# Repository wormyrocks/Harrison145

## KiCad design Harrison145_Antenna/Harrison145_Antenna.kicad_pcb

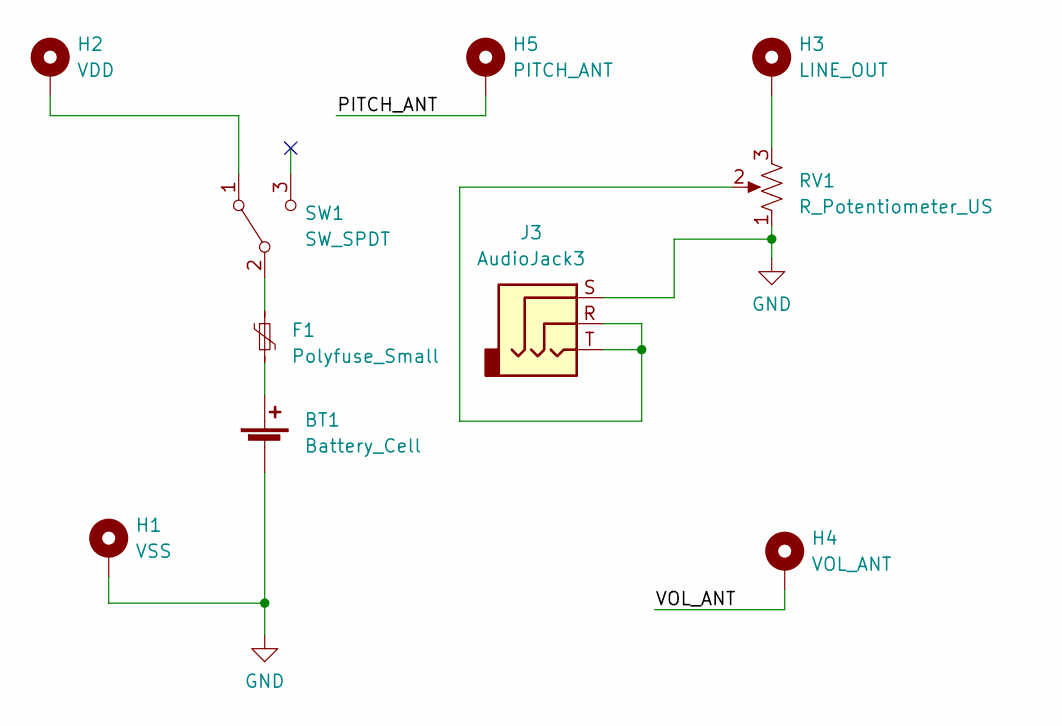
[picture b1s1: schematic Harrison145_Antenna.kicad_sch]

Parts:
BT1: Battery_Cell; 9V_Bat
F1: Polyfuse_Small; Fuse_1812_4532Metric_Pad1.30x3.40mm_HandSolder
H1: VSS; SMTSO-M4
H2: VDD; SMTSO-M4
H3: LINE_OUT; SMTSO-M4
H4: VOL_ANT; SMTSO-M4
H5: PITCH_ANT; SMTSO-M4
J3: AudioJack3; Jack_3.5mm_CUI_SJ-3523-SMT_Horizontal
RV1: R_Potentiometer_US; PTV09A3015FB103
SW1: SW_SPDT; CSS1210TB

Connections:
/PITCH_ANT: H5.1
/VOL_ANT: H4.1
GND: BT1.2 (-), H1.1, J3.S, RV1.1
unnamed: BT1.1 (+), F1.2
unnamed: H3.1, RV1.3
unnamed: J3.R, J3.T, RV1.2
unnamed: H2.1, SW1.1 (A)
unnamed: F1.1, SW1.2 (B)

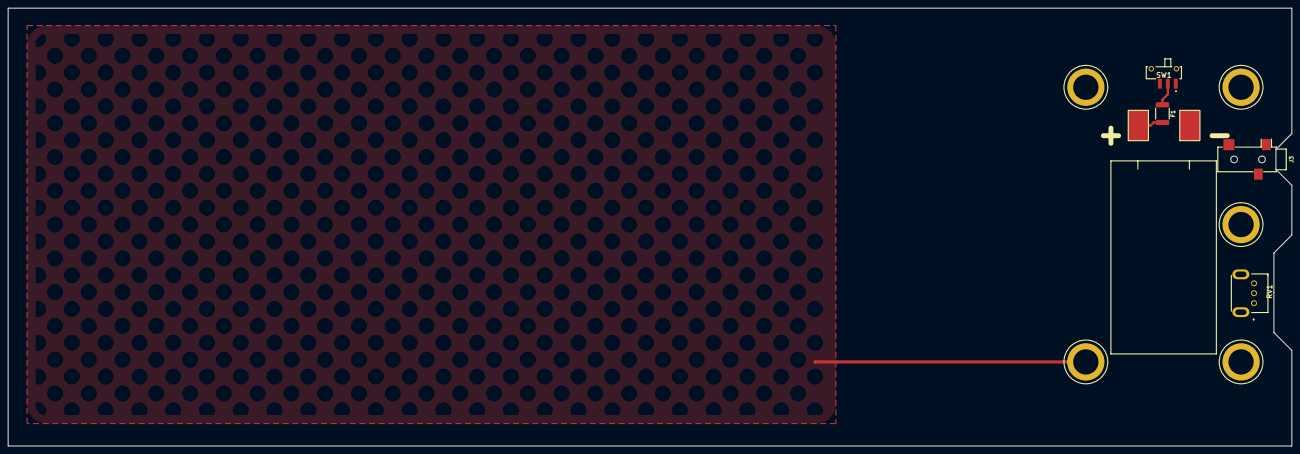
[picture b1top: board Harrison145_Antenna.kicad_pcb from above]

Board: 2 copper layers, 322.5 x 110.0 mm, 10 parts (0 on the bottom side), 6 nets.

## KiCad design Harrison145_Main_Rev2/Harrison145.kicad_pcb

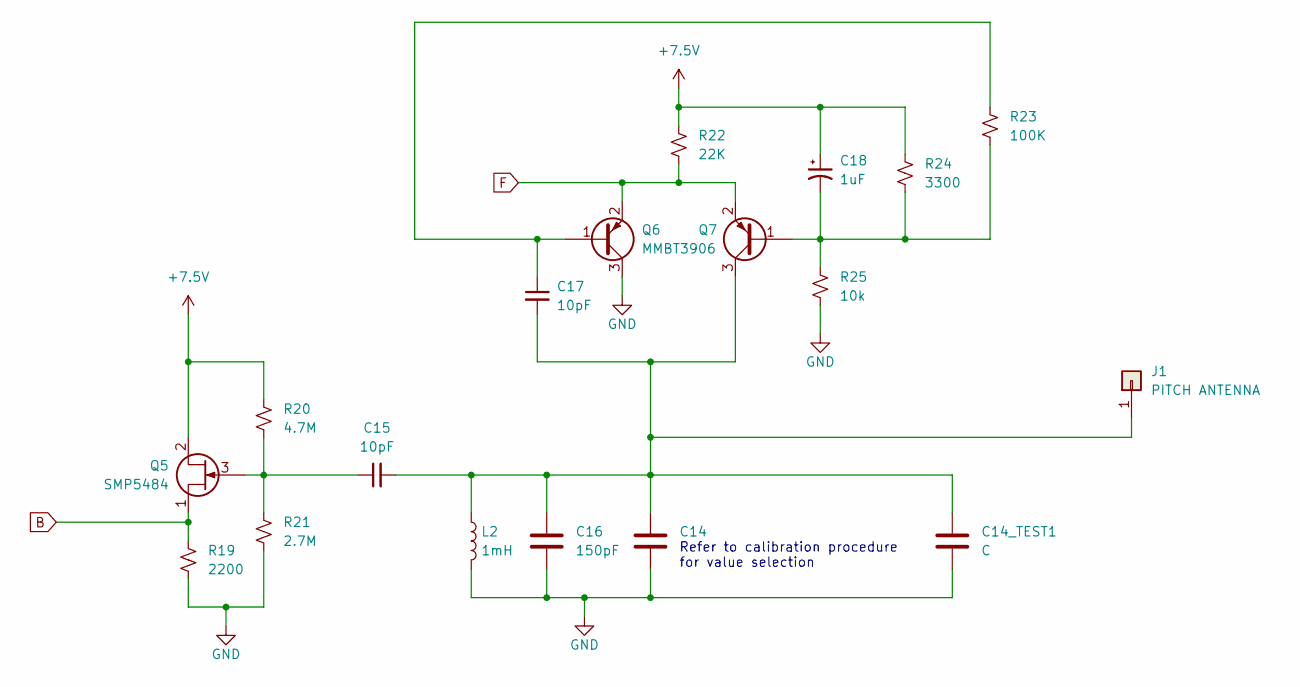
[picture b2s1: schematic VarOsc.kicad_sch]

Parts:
C14: C_Mica; C_0805_2012Metric_Pad1.18x1.45mm_HandSolder
C14_TEST1: C; C_Disc_D3.0mm_W1.6mm_P2.50mm
C15, C17: 10pF; C_0603_1608Metric
C16: 150pF; C_1210_3225Metric_Pad1.33x2.70mm_HandSolder
C18: 1uF; CP_EIA-2012-12_Kemet-R_Pad1.30x1.05mm_HandSolder
J1: PITCH ANTENNA; MountingHole_4.3mm_M4_Pad_Via
L2: 1mH; L_1812_4532Metric
Q5: SMP5484; SOT-23
Q6, Q7: MMBT3906; SOT-23
R19: 2200; R_0603_1608Metric
R20: 4.7M; R_0603_1608Metric
R21: 2.7M; R_0603_1608Metric
R22: 22K; R_0603_1608Metric
R23: 100K; R_0603_1608Metric
R24: 3300; R_0603_1608Metric
R25: 10k; R_0603_1608Metric

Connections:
+7.5V: C18.1, Q5.2 (D), R20.1, R22.1, R24.1; also elsewhere on the board
B: Q5.1 (S), R19.1; also elsewhere on the board
F: Q6.2 (E), Q7.2 (E), R22.2; also elsewhere on the board
GND: C14.2, C14_TEST1.2, C16.2, L2.2, Q6.3 (C), R19.2, R21.2, R25.2; also elsewhere on the board
unnamed: C14.1, C14_TEST1.1, C15.2, C16.1, C17.2, J1.1, L2.1, Q7.3 (C)
unnamed: C15.1, Q5.3 (G), R20.2, R21.1
unnamed: C17.1, Q6.1 (B), R23.1
unnamed: C18.2, Q7.1 (B), R23.2, R24.2, R25.1

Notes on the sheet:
Refer to calibration procedure for value selection

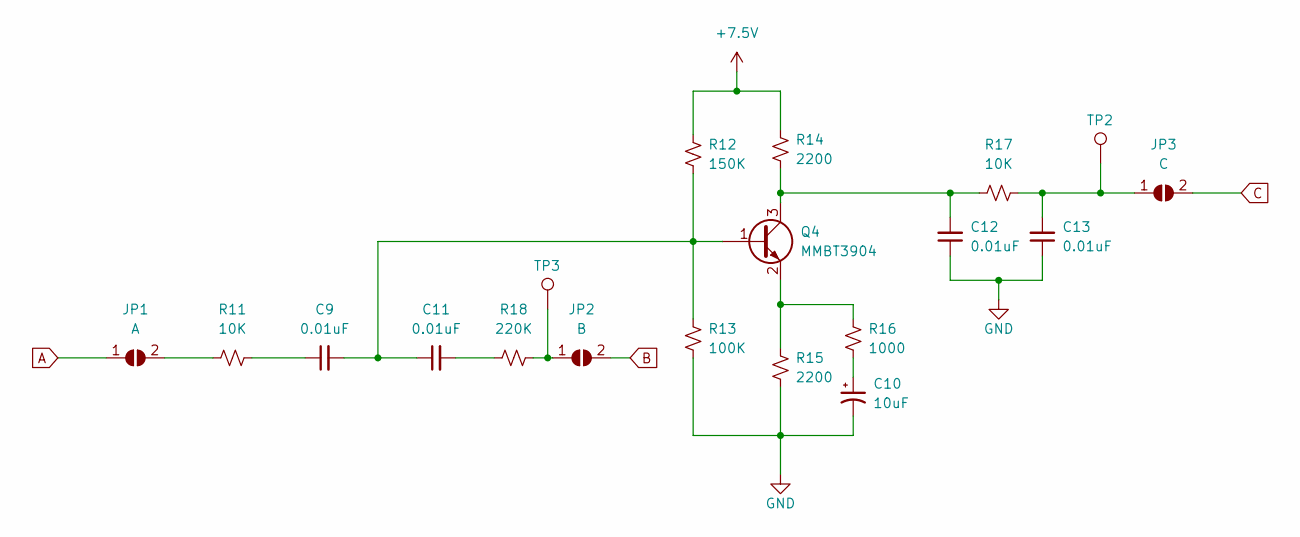
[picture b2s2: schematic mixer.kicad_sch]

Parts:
C9, C11, C12, C13: 0.01uF; C_0603_1608Metric
C10: 10uF; CP_EIA-3216-18_Kemet-A
JP1: A; SolderJumper-2_P1.3mm_Open_RoundedPad1.0x1.5mm
JP2: B; SolderJumper-2_P1.3mm_Open_RoundedPad1.0x1.5mm
JP3: C; SolderJumper-2_P1.3mm_Open_RoundedPad1.0x1.5mm
Q4: MMBT3904; SOT-23
R11, R17: 10K; R_0603_1608Metric
R12: 150K; R_0603_1608Metric
R13: 100K; R_0603_1608Metric
R14, R15: 2200; R_0603_1608Metric
R16: 1000; R_0603_1608Metric
R18: 220K; R_0603_1608Metric
TP2, TP3: TestPoint; TestPoint_Loop_D1.80mm_Drill1.0mm_Beaded

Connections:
+7.5V: R12.2, R14.2; also elsewhere on the board
A: JP1.1 (A); also elsewhere on the board
B: JP2.2 (B); also elsewhere on the board
C: JP3.2 (B); also elsewhere on the board
GND: C10.2, C12.1, C13.1, R13.1, R15.1; also elsewhere on the board
unnamed: C9.1, R11.2
unnamed: C10.1, R16.1
unnamed: C11.2, R18.1
unnamed: JP1.2 (B), R11.1
unnamed: JP2.1 (A), R18.2, TP3.1
unnamed: C13.2, JP3.1 (A), R17.2, TP2.1
unnamed: C9.2, C11.1, Q4.1 (B), R12.1, R13.2
unnamed: C12.2, Q4.3 (C), R14.1, R17.1
unnamed: Q4.2 (E), R15.2, R16.2

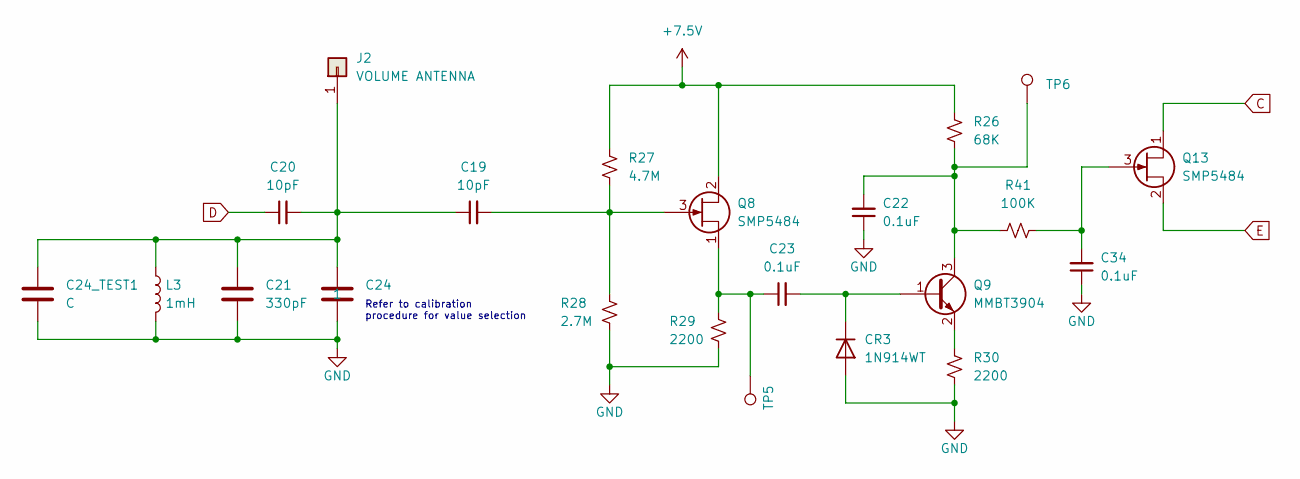
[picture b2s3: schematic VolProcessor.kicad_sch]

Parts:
C19, C20: 10pF; C_0603_1608Metric
C21: 330pF; C_1812_4532Metric_Pad1.57x3.40mm_HandSolder
C22, C23, C34: 0.1uF; C_0603_1608Metric
C24: C_Mica; C_0805_2012Metric_Pad1.18x1.45mm_HandSolder
C24_TEST1: C; C_Disc_D3.0mm_W1.6mm_P2.50mm
CR3: 1N914WT; D_SOD-523
J2: VOLUME ANTENNA; MountingHole_4.3mm_M4_Pad_Via
L3: 1mH; L_1812_4532Metric
Q8, Q13: SMP5484; SOT-23
Q9: MMBT3904; SOT-23
R26: 68K; R_0603_1608Metric
R27: 4.7M; R_0603_1608Metric
R28: 2.7M; R_0603_1608Metric
R29, R30: 2200; R_0603_1608Metric
R41: 100K; R_0603_1608Metric
TP5, TP6: TestPoint; TestPoint_Loop_D1.80mm_Drill1.0mm_Beaded

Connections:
+7.5V: Q8.2 (D), R26.1, R27.1; also elsewhere on the board
C: Q13.1 (S); also elsewhere on the board
D: C20.1; also elsewhere on the board
E: Q13.2 (D); also elsewhere on the board
GND: C21.2, C22.1, C24.2, C24_TEST1.2, C34.1, CR3.2 (A), L3.2, R28.2, R29.2, R30.2; also elsewhere on the board
unnamed: C23.2, CR3.1 (K), Q9.1 (B)
unnamed: C19.1, C20.2, C21.1, C24.1, C24_TEST1.1, J2.1, L3.1
unnamed: C19.2, Q8.3 (G), R27.2, R28.1
unnamed: C23.1, Q8.1 (S), R29.1, TP5.1
unnamed: C22.2, Q9.3 (C), R26.2, R41.1, TP6.1
unnamed: Q9.2 (E), R30.1
unnamed: C34.2, Q13.3 (G), R41.2

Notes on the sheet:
Refer to calibration procedure for value selection

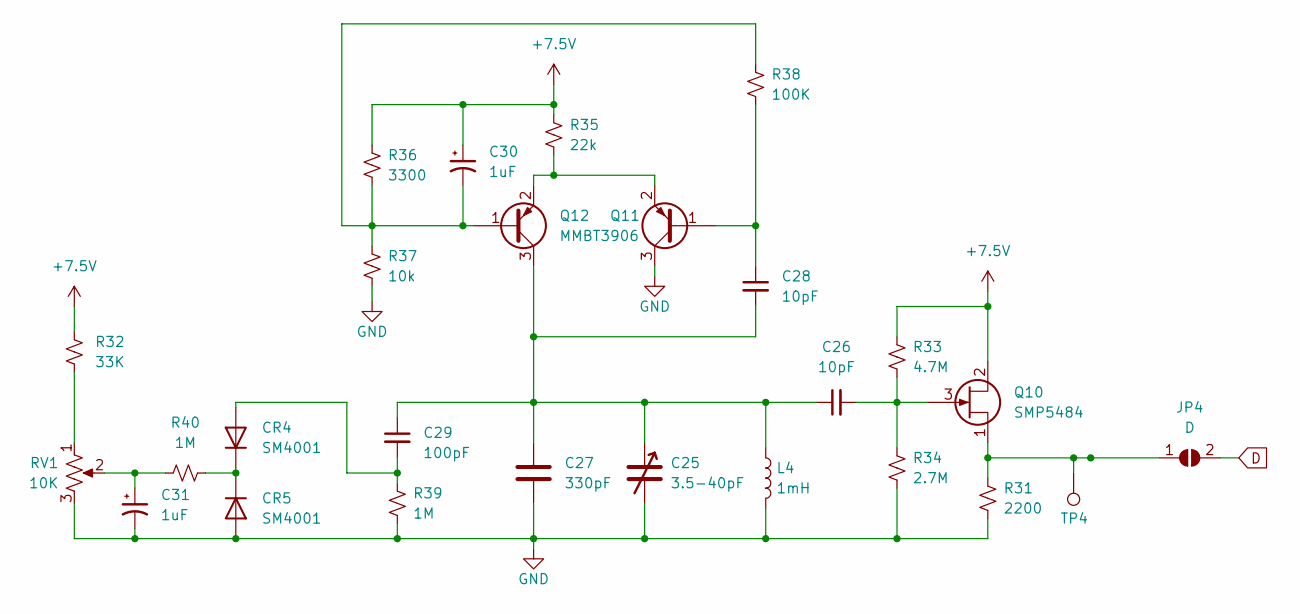
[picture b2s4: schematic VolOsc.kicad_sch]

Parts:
C25: 3.5-40pF; CAPV_JZ400
C26, C28: 10pF; C_0603_1608Metric
C27: 330pF; C_1812_4532Metric_Pad1.57x3.40mm_HandSolder
C29: 100pF; C_0603_1608Metric
C30, C31: 1uF; CP_EIA-2012-12_Kemet-R_Pad1.30x1.05mm_HandSolder
CR4, CR5: SM4001; D_MELF
JP4: D; SolderJumper-2_P1.3mm_Open_RoundedPad1.0x1.5mm
L4: 1mH; L_1812_4532Metric
Q10: SMP5484; SOT-23
Q11, Q12: MMBT3906; SOT-23
R31: 2200; R_0603_1608Metric
R32: 33K; R_0603_1608Metric
R33: 4.7M; R_0603_1608Metric
R34: 2.7M; R_0603_1608Metric
R35: 22k; R_0603_1608Metric
R36: 3300; R_0603_1608Metric
R37: 10k; R_0603_1608Metric
R38: 100K; R_0603_1608Metric
R39, R40: 1M; R_0603_1608Metric
RV1: 10K; PTV09A3015FB103
TP4: TestPoint; TestPoint_Loop_D1.80mm_Drill1.0mm_Beaded

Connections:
+7.5V: C30.1, Q10.2 (D), R32.1, R33.1, R35.2, R36.1; also elsewhere on the board
D: JP4.2 (B); also elsewhere on the board
GND: C25.2, C27.2, C31.2, CR5.2 (A), L4.2, Q11.3 (C), R31.2, R34.2, R37.2, R39.2, RV1.3; also elsewhere on the board
unnamed: C31.1, R40.1, RV1.2
unnamed: C29.2, CR4.2 (A), R39.1
unnamed: CR4.1 (K), CR5.1 (K), R40.2
unnamed: JP4.1 (A), Q10.1 (S), R31.1, TP4.1
unnamed: C26.2, Q10.3 (G), R33.2, R34.1
unnamed: C28.1, Q11.1 (B), R38.2
unnamed: Q11.2 (E), Q12.2 (E), R35.1
unnamed: C30.2, Q12.1 (B), R36.2, R37.1, R38.1
unnamed: C25.1, C26.1, C27.1, C28.2, C29.1, L4.1, Q12.3 (C)
unnamed: R32.2, RV1.1

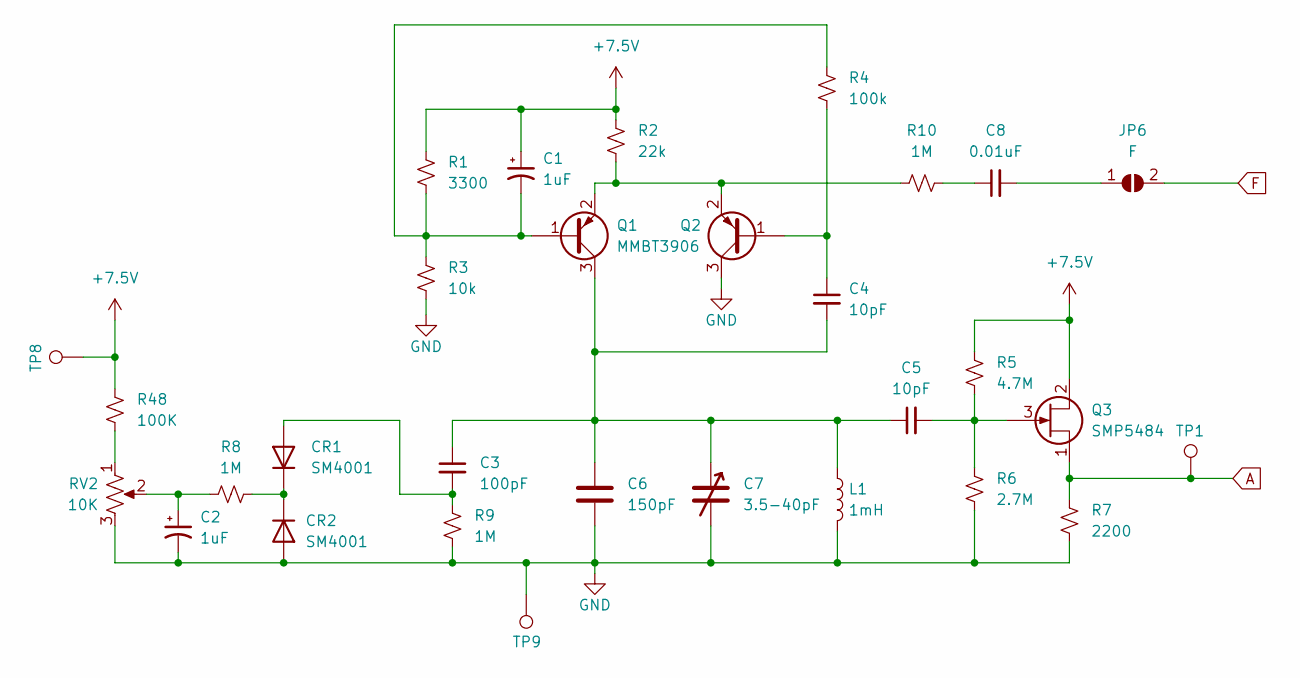
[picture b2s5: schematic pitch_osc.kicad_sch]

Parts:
C1, C2: 1uF; CP_EIA-2012-12_Kemet-R_Pad1.30x1.05mm_HandSolder
C3: 100pF; C_0603_1608Metric
C4, C5: 10pF; C_0603_1608Metric
C6: 150pF; C_1210_3225Metric_Pad1.33x2.70mm_HandSolder
C7: 3.5-40pF; CAPV_JZ400
C8: 0.01uF; C_0603_1608Metric
CR1, CR2: SM4001; D_MELF
JP6: F; SolderJumper-2_P1.3mm_Open_RoundedPad1.0x1.5mm
L1: 1mH; L_1812_4532Metric
Q1, Q2: MMBT3906; SOT-23
Q3: SMP5484; SOT-23
R1: 3300; R_0603_1608Metric
R2: 22k; R_0603_1608Metric
R3: 10k; R_0603_1608Metric
R4: 100k; R_0603_1608Metric
R5: 4.7M; R_0603_1608Metric
R6: 2.7M; R_0603_1608Metric
R7: 2200; R_0603_1608Metric
R8, R9, R10: 1M; R_0603_1608Metric
R48: 100K; R_0603_1608Metric
RV2: 10K; PTV09A3015FB103
TP1, TP8, TP9: TestPoint; TestPoint_Loop_D1.80mm_Drill1.0mm_Beaded

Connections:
+7.5V: C1.1, Q3.2 (D), R1.1, R2.2, R5.1, R48.1, TP8.1; also elsewhere on the board
A: Q3.1 (S), R7.1, TP1.1; also elsewhere on the board
F: JP6.2 (B); also elsewhere on the board
GND: C2.2, C6.2, C7.2, CR2.2 (A), L1.2, Q2.3 (C), R3.2, R6.2, R7.2, R9.2, RV2.3, TP9.1; also elsewhere on the board
unnamed: C2.1, R8.1, RV2.2
unnamed: C8.1, R10.2
unnamed: C3.2, CR1.2 (A), R9.1
unnamed: CR1.1 (K), CR2.1 (K), R8.2
unnamed: C8.2, JP6.1 (A)
unnamed: C1.2, Q1.1 (B), R1.2, R3.1, R4.1
unnamed: C3.1, C4.2, C5.1, C6.1, C7.1, L1.1, Q1.3 (C)
unnamed: Q1.2 (E), Q2.2 (E), R2.1, R10.1
unnamed: C4.1, Q2.1 (B), R4.2
unnamed: C5.2, Q3.3 (G), R5.2, R6.1
unnamed: R48.2, RV2.1

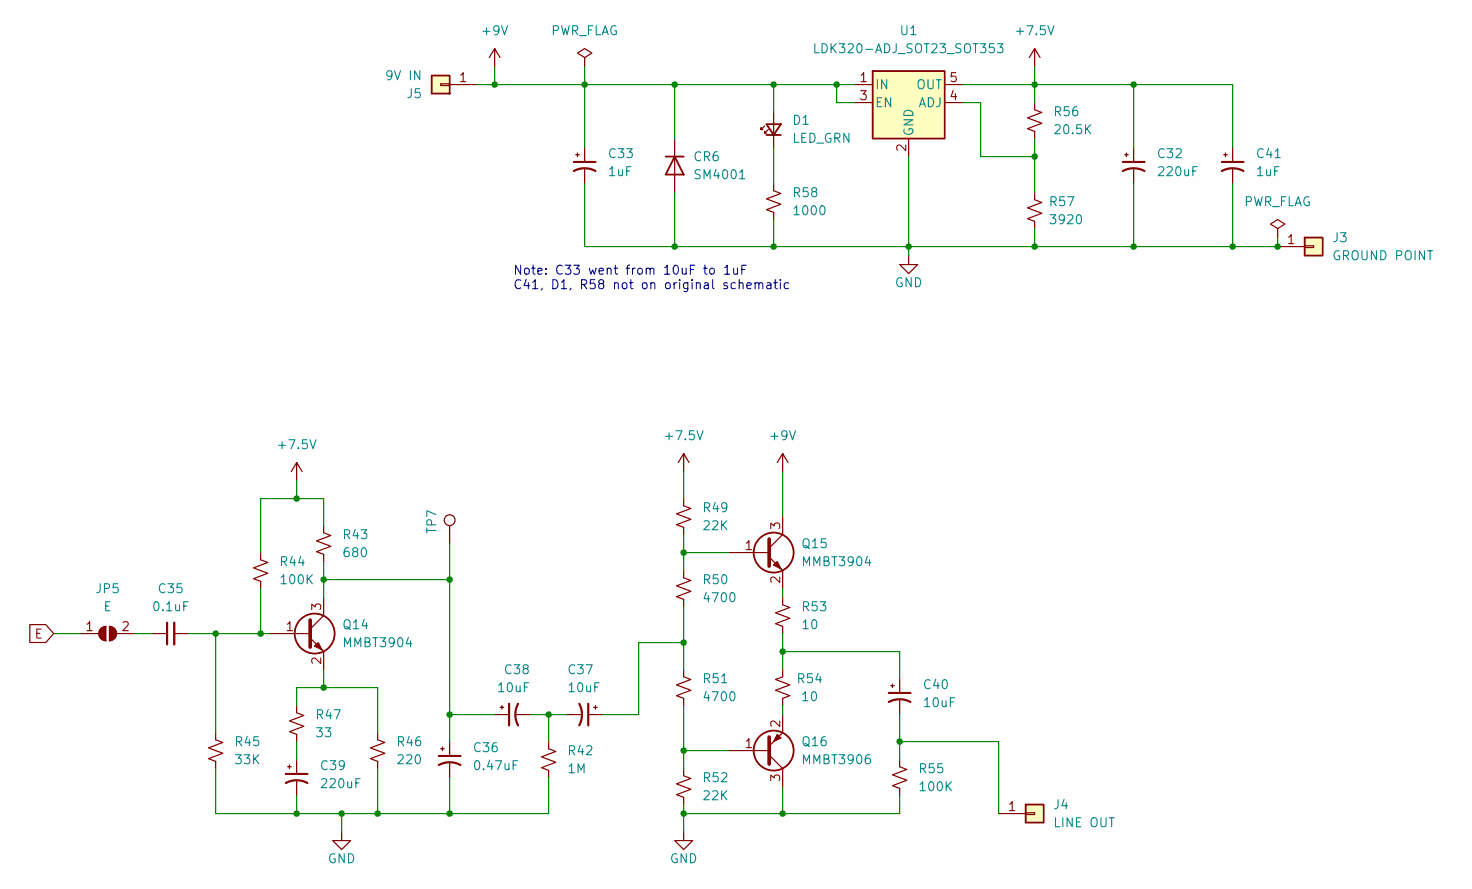
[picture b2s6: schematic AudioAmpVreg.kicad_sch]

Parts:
C32, C39: 220uF; CP_Elec_6.3x5.9
C33, C41: 1uF; CP_EIA-2012-12_Kemet-R_Pad1.30x1.05mm_HandSolder
C35: 0.1uF; C_0603_1608Metric
C36: 0.47uF; CP_EIA-1608-08_AVX-J
C37, C38, C40: 10uF; CP_EIA-3216-18_Kemet-A
CR6: SM4001; D_MELF
D1: LED_GRN; LED_0603_1608Metric_Pad1.05x0.95mm_HandSolder
J3: GROUND POINT; MountingHole_4.3mm_M4_Pad_Via
J4: LINE OUT; MountingHole_4.3mm_M4_Pad_Via
J5: 9V IN; MountingHole_4.3mm_M4_Pad_Via
JP5: E; SolderJumper-2_P1.3mm_Open_RoundedPad1.0x1.5mm
Q14, Q15: MMBT3904; SOT-23
Q16: MMBT3906; SOT-23
R42: 1M; R_0603_1608Metric
R43: 680; R_0603_1608Metric
R44, R55: 100K; R_0603_1608Metric
R45: 33K; R_0603_1608Metric
R46: 220; R_0603_1608Metric
R47: 33; R_0603_1608Metric
R49, R52: 22K; R_0603_1608Metric
R50, R51: 4700; R_0603_1608Metric
R53, R54: 10; R_0603_1608Metric
R56: 20.5K; R_0603_1608Metric
R57: 3920; R_0603_1608Metric
R58: 1000; R_0603_1608Metric
TP7: TestPoint; TestPoint_Loop_D1.80mm_Drill1.0mm_Beaded
U1: LDK320-ADJ_SOT23_SOT353; SOT-23-5

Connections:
+7.5V: C32.1, C41.1, R43.2, R44.1, R49.1, R56.1, U1.5 (OUT); also elsewhere on the board
+9V: C33.1, CR6.1 (K), D1.2 (A), J5.1, Q15.3 (C), U1.1 (IN), U1.3 (EN)
E: JP5.1 (A); also elsewhere on the board
GND: C32.2, C33.2, C36.2, C39.2, C41.2, CR6.2 (A), J3.1, Q16.3 (C), R42.2, R45.2, R46.2, R52.2, R55.2, R57.2, R58.2, U1.2 (GND); also elsewhere on the board
unnamed: C37.1, R50.2, R51.2
unnamed: C37.2, C38.2, R42.1
unnamed: C39.1, R47.2
unnamed: C40.1, R53.1, R54.2
unnamed: D1.1 (K), R58.1
unnamed: C40.2, J4.1, R55.1
unnamed: C35.1, JP5.2 (B)
unnamed: C35.2, Q14.1 (B), R44.2, R45.1
unnamed: C36.1, C38.1, Q14.3 (C), R43.1, TP7.1
unnamed: Q14.2 (E), R46.1, R47.1
unnamed: Q15.1 (B), R49.2, R50.1
unnamed: Q15.2 (E), R53.2
unnamed: Q16.1 (B), R51.1, R52.1
unnamed: Q16.2 (E), R54.1
unnamed: R56.2, R57.1, U1.4 (ADJ)

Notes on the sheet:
Note: C33 went from 10uF to 1uF C41, D1, R58 not on original schematic

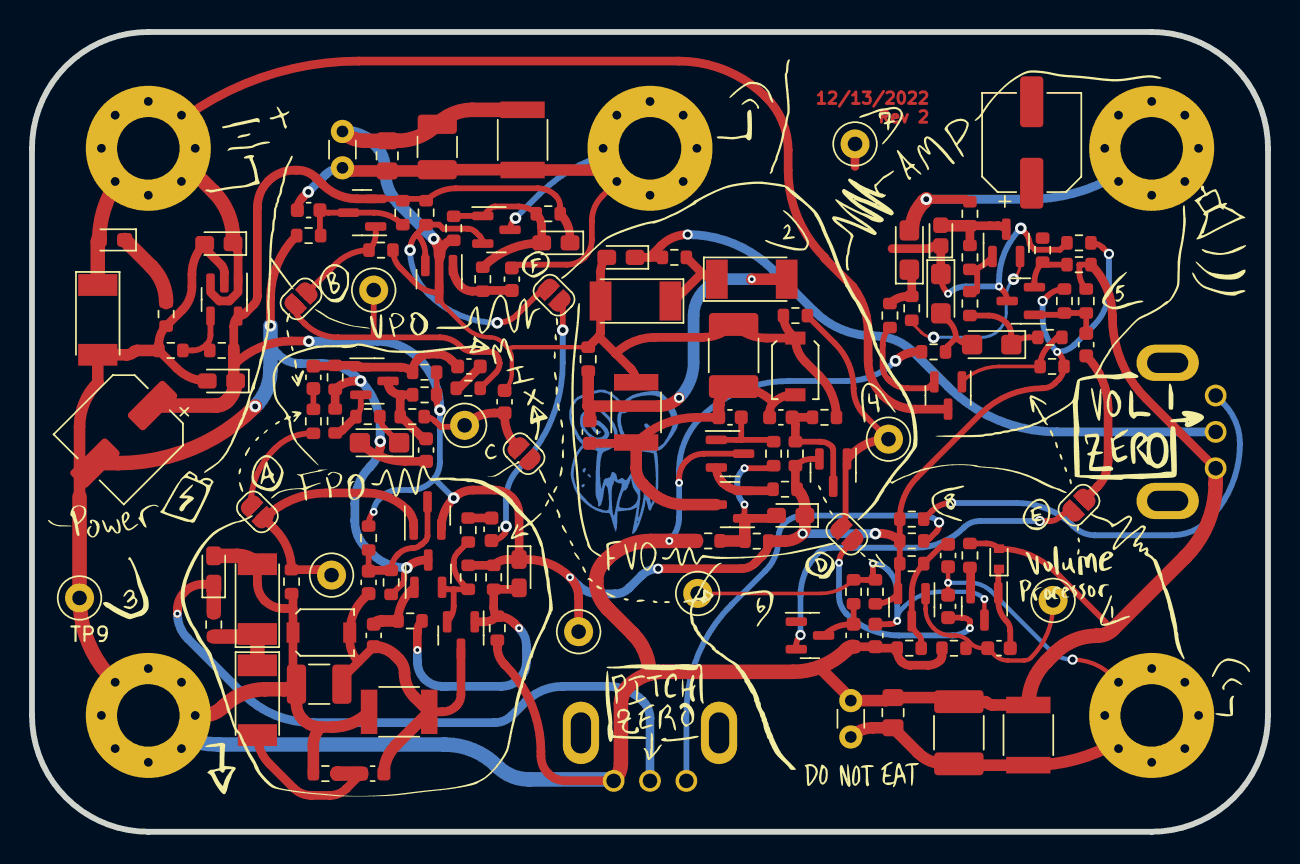
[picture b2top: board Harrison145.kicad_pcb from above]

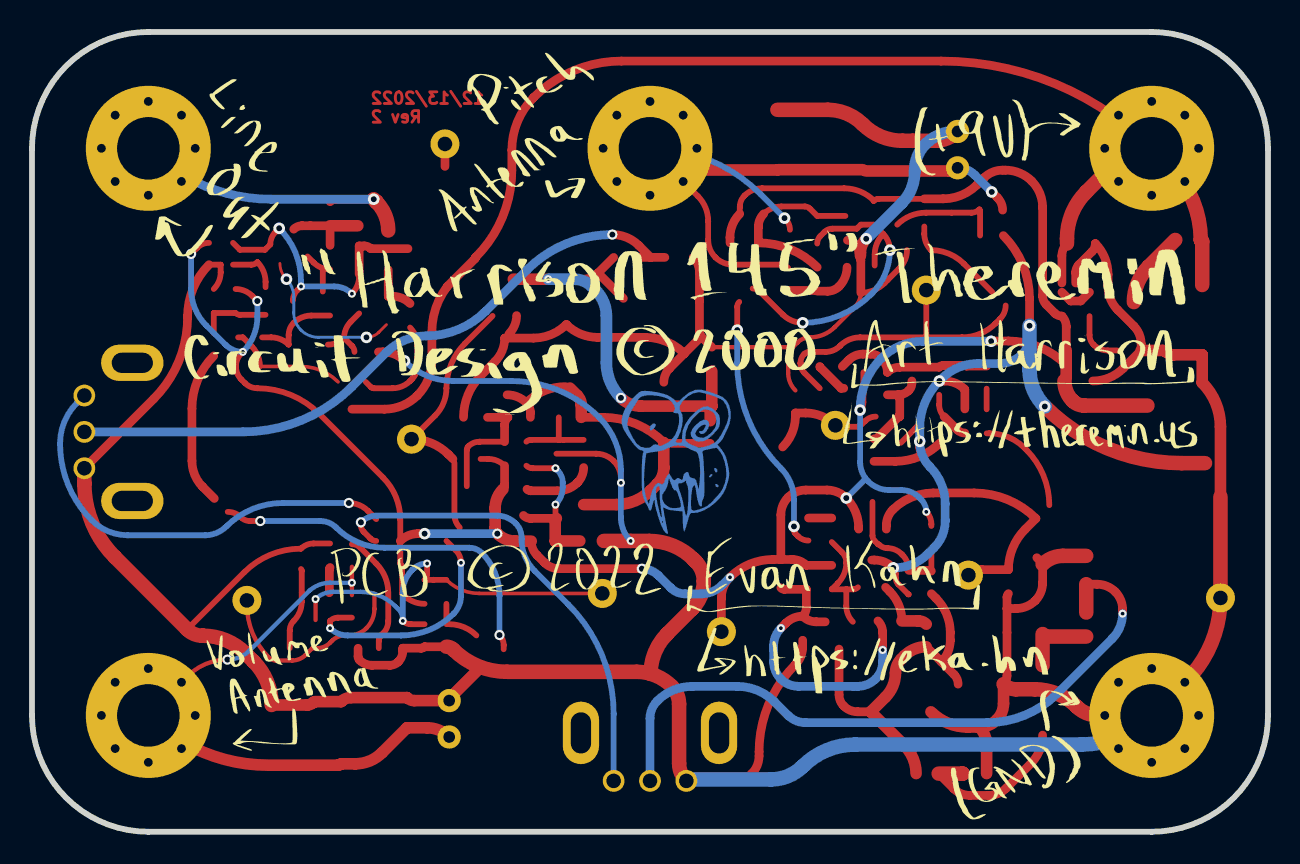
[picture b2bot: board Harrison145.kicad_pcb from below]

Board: 2 copper layers, 85.0 x 55.0 mm, 152 parts (2 on the bottom side), 65 nets.

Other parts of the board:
Ge: LOGO; FrontSilk

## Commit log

2022-12-08 Components mostly placed
2022-12-10 Revisions
2022-12-10 Better component placements
2022-12-11 Mostly routed
2022-12-12 Routing finished, still needs to pass DRC
2022-12-12 Improved DRC
2022-12-12 Reduced silk designators; DRC passes
2022-12-13 Added aseprite backgrounds
2022-12-13 All DRC/ERC that matters passes
2022-12-13 Added mouser part links
2022-12-13 Added BOM and Mouser BOM
2022-12-13 Added revision number
2022-12-14 antenna outline
2022-12-14 Added iBOM
2022-12-14 Added antenna project
2023-01-02 Added Errata notes
2023-01-08 Initial commit for rev2 main pcb
    * Thicken up some ground traces
    * Change to Coilcraft inductors
    * Change to aluminum polymer caps
    * Update project to KiCAD 6.99 format
2023-01-09 Update rev2 kicad_pcb
2023-01-09 Antenna design changes
2023-01-09 Combine 9V battery and terminals into a single footprint
2023-01-10 Small updates
    * Edited Errata
    * Changed VReg resistor from 20k to 20.5k
    * Changed ceramic cap symbols incorrectly listed as polarized
2023-01-11 Progress on bringup of simulations in KiCAD 6 and KiCAD 7
2023-01-14 Add handcrafted ngspice netlist
2023-01-15 ngspice model: actually works
2023-01-15 Broken commit
2023-01-15 Working, fixed SPICE model
2023-01-15 small changes
2023-01-19 Add VPO sim, untested
2023-01-19 Added FVO, other minor fixes
    * Add some to-dos
    * Add missing R9
    * Add hand capacitance to VPO
2023-01-20 Add VVO, amp, and mixer (all untested)
2023-01-20 'Interference pattern' antenna design
2023-01-20 Added step files for full antenna assembly
2023-01-24 Fixed VPO netlist
2023-01-25 Reorganized into control and display files
2023-01-25 Added TP4 frequency analysis and expectations vs reality on oscillator swing
2023-01-25 Remove kicad sims
2023-01-25 Added screenshots of test captures
2023-02-07 Cutouts on antenna pcb
2023-02-08 Silk and copper art
2023-02-11 Antenna ordered from JLCPCB
